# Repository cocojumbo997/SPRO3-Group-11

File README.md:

# SPRO3 Group 11 GitHub

## Repository Structure

- **Master Branch**  
  The `master` branch contains the **ROS2 workspace (ros_ws)** and all related files necessary for the ROS2 project.  

- **Main Branch**  
  The `main` branch is designated for **all other files**, such as datasheets, Arduino code, and KiCAD files.

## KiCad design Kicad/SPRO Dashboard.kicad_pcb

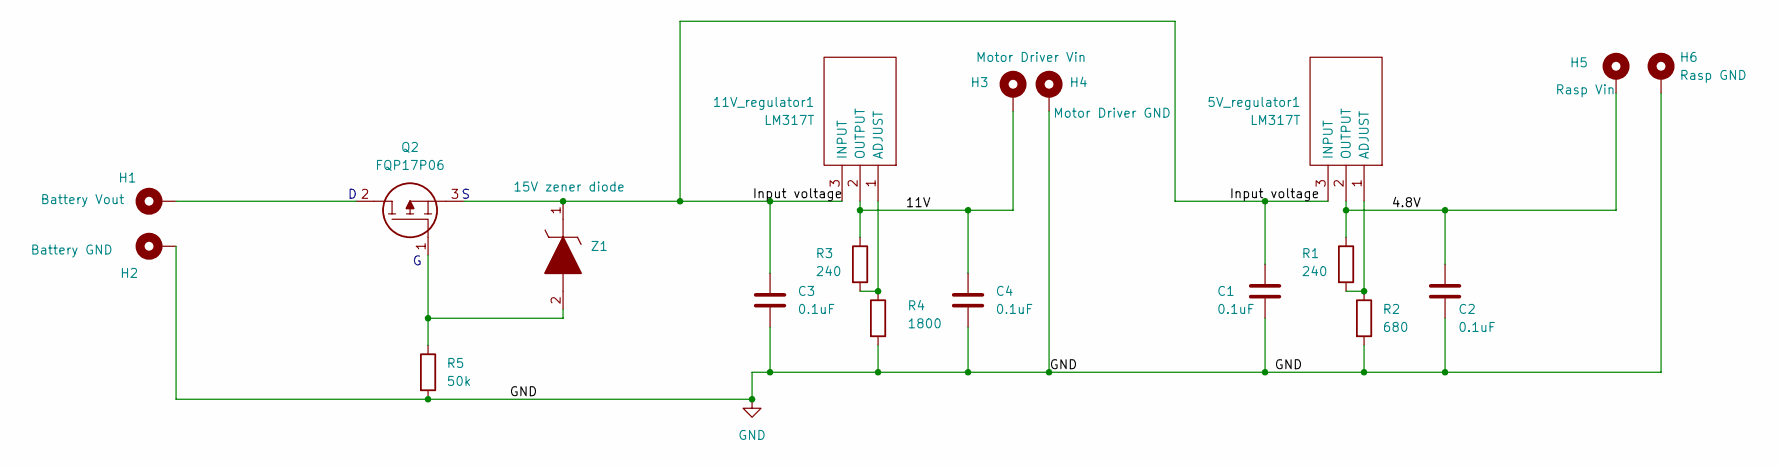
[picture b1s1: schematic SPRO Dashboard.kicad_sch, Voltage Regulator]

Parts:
5V_regulator1, 11V_regulator1: LM317T; TO255P460X1020X2008-3P; Mouser Part Number 511-LM317T
C1, C2, C3, C4: 0.1uF; C_Axial_L5.1mm_D3.1mm_P7.50mm_Horizontal
H1: Battery Vout; SolderWire-0.1sqmm_1x01_D0.4mm_OD1mm
H2: Battery GND; SolderWire-0.1sqmm_1x01_D0.4mm_OD1mm
H3: Motor Driver Vin; SolderWire-0.1sqmm_1x01_D0.4mm_OD1mm
H4: Motor Driver GND; SolderWire-0.1sqmm_1x01_D0.4mm_OD1mm
H5: Rasp Vin; SolderWire-0.1sqmm_1x01_D0.4mm_OD1mm
H6: Rasp GND; SolderWire-0.1sqmm_1x01_D0.4mm_OD1mm
Q2: FQP17P06; TO254P470X1016X2019-3P; Mouser Part Number 512-FQP17P06
R1, R3: 240; R_Axial_DIN0309_L9.0mm_D3.2mm_P12.70mm_Horizontal
R2: 680; R_Axial_DIN0309_L9.0mm_D3.2mm_P12.70mm_Horizontal
R4: 1800; R_Axial_DIN0309_L9.0mm_D3.2mm_P12.70mm_Horizontal
R5: 50k; R_Axial_DIN0309_L9.0mm_D3.2mm_P12.70mm_Horizontal
Z1: 15V zener diode; DIOAD950W60L350D150; Mouser Part Number 78-BZX55C10-TAP

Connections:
/4.8V: 5V_regulator1.2 (OUTPUT), C2.1, H5.1, R1.1
/11V: 11V_regulator1.2 (OUTPUT), C4.1, H3.1, R3.1
/Input voltage: 5V_regulator1.3 (INPUT), 11V_regulator1.3 (INPUT), C1.1, C3.1, Q2.3, Z1.1
GND: C1.2, C2.2, C3.2, C4.2, H2.1, H4.1, H6.1, R2.2, R4.2, R5.2
unnamed: 5V_regulator1.1 (ADJUST), R1.2, R2.1
unnamed: 11V_regulator1.1 (ADJUST), R3.2, R4.1
unnamed: H1.1, Q2.2
unnamed: Q2.1, R5.1, Z1.2

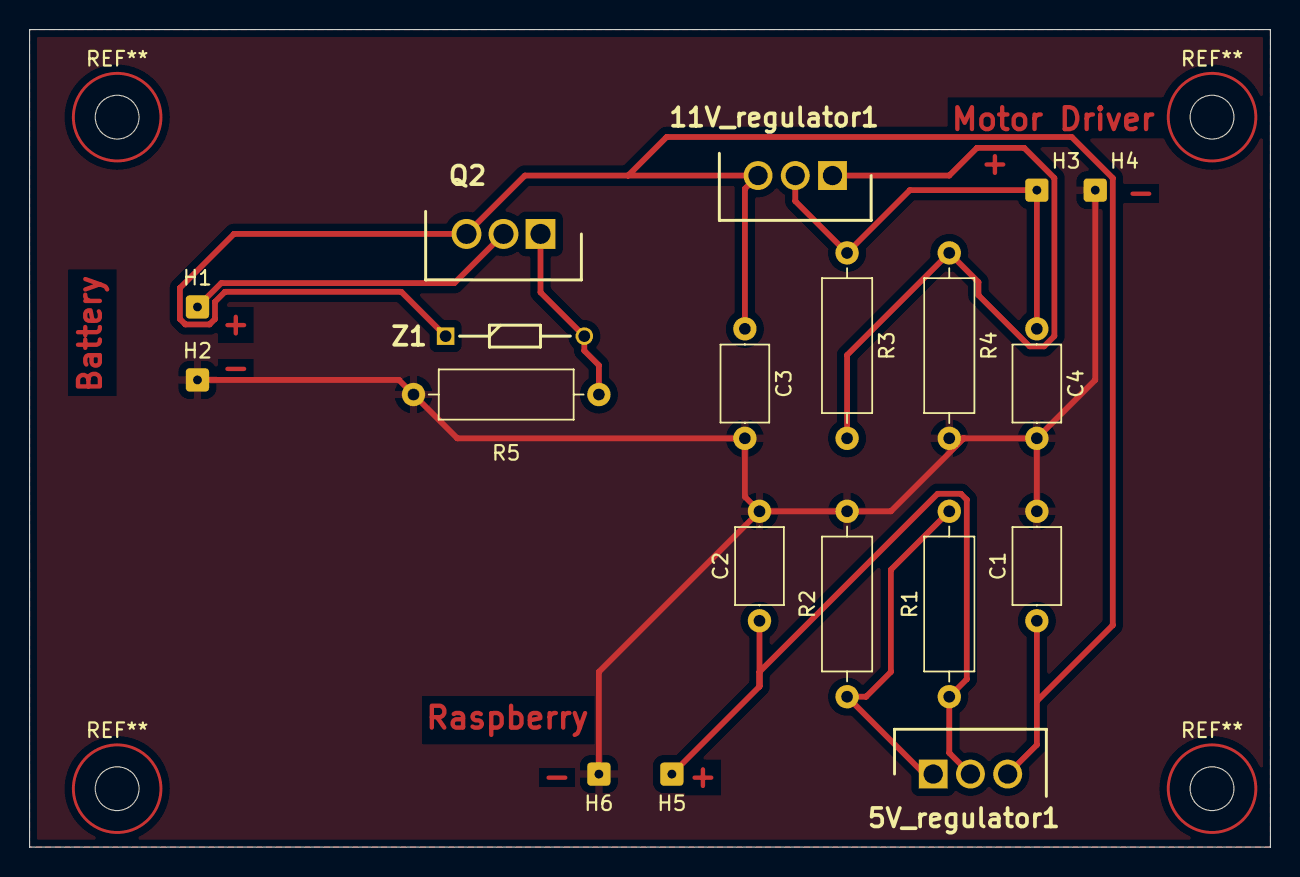
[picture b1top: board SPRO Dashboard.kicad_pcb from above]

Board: 2 copper layers, 85.0 x 56.0 mm, 19 parts (0 on the bottom side), 8 nets.

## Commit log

2024-12-09 Create ros2_ws
    create folder for ros2 files
2024-12-09 upload files
2024-12-09 Added LM317 datasheet
2024-12-09 Uploaded Raspberry datasheet
2024-12-09 Add LD06 datasheet
2024-12-09 Added IMU MPU-6050 datasheet
2024-12-12 added battery datasheet
2024-12-12 Added LetsOKdo LiDAR datasheet
2024-12-13 Added PCB files
2024-12-14 Uploaded diode and voltage regulator datasheets
2024-12-14 Add diode datasheet
2024-12-23 Added Myzhar's driver files
    Added Myzhar's LiDAR Driver files. For proper usage, manual installation is still recommended.
